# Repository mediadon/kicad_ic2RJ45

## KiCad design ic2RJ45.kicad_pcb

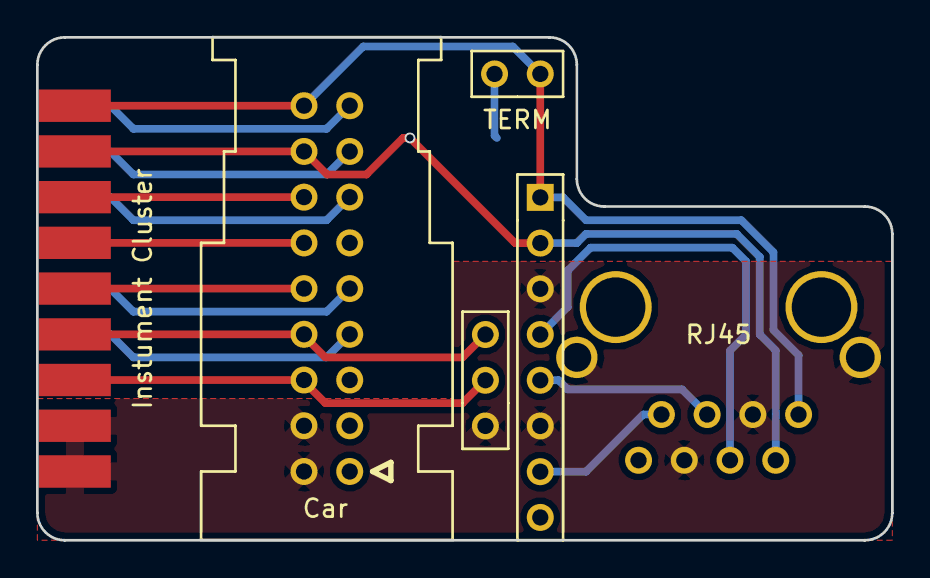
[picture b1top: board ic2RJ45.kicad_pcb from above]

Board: 2 copper layers, 47.5 x 27.9 mm, 7 parts (1 on the bottom side), 18 nets.

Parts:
.: Car; IC_CONN_02x09
.#2: TERM; Pin_Header_Straight_2x01
.#3: Instument Cluster; IC_CONN_02x09_axial
J1: RJ45; RJ45_Pollin
P1: .; Pin_Header_Straight_1x03
P3: .; Pin_Header_Straight_1x08
R1: 120; Resistor_SMDuniversal_0805to1206_HandSoldering

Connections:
GND: ..10, ..11, .#3.10, .#3.11, J1.3, J1.6, J1.9, P1.1, P3.3, P3.6
unnamed: ..4, .#3.4
unnamed: ..5, .#3.5
unnamed: ..7, .#3.7
unnamed: ..8, .#3.8
unnamed: ..9, .#3.9
unnamed: ..12, .#3.12, P1.2
unnamed: ..13, .#3.13, P1.3
unnamed: ..14, .#3.14
unnamed: ..15, .#3.15
unnamed: ..16, .#3.16
unnamed: ..17, .#3.17, J1.2, P3.2, R1.2
unnamed: ..18, .#2.2, .#3.18, J1.1, P3.1
unnamed: J1.4, P3.4
unnamed: J1.5, P3.5
unnamed: J1.7, P3.7
unnamed: .#2.1, R1.1
VCC: ..1, .#3.1, J1.8, P3.8

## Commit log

2017-02-01 Clean Project.
2017-02-01 Schematic and netlist added.
2017-02-01 further design modifications
2017-02-01 finalized v1.1

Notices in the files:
ic2RJ45.kicad_pcb:
© Daniel Laffling 2017
